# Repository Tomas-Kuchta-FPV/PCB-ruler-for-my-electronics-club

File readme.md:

# Thomases PCB ruler

So I run an electronics club in my chool and I want for the kids to have something fun. So I've figured that PCB rulers will cut ir, because we don't get many of these here.  
The front side has all of the basic schematic symbols, a ruller and a RFID detector.  
And what about the back side? It's pure ADHD riddeled with cool graphics, tables and more advanced footprints.  

## BOM
| Item               | Price ($)  | Link                                                      |
| ------------------ | ---------- | --------------------------------------------------------- |
| 0603 67R Rezistor  | Negligible | https://www.lcsc.com/product-detail/C2909394.html         |
| 0603 LED Diode     | Negligible | https://www.lcsc.com/product-detail/C19171394.html        |
| JLCPCB fabrication | 13.8       | https://cart.jlcpcb.com/quote                             |
| Duties and Taxes   | 8.2        | https://jlcpcb.com/shipping                               |
| Shipping           | 8.7        | https://jlcpcb.com/help/article/customs,-duties-and-taxes |
| Total              | 30.7       |

## Inspiration & Atribution
https://github.com/notaroomba/trace  
https://github.com/Small-doge128/swag-PCB-ruler  
Clipartt from https://www.svgrepo.com/collection/ionicons-filled-interface-icons/, https://www.svgrepo.com/collection/zest-interface-icons/ and https://www.svgrepo.com/collection/insects-1/

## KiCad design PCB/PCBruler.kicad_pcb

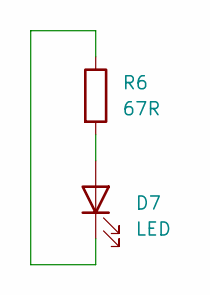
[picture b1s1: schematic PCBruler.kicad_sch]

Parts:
D7: LED; LED_0603_1608Metric
R6: 67R; R_0603_1608Metric_Pad0.98x0.95mm_HandSolder

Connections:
unnamed: D7.2 (A), R6.2
unnamed: D7.1 (K), R6.1

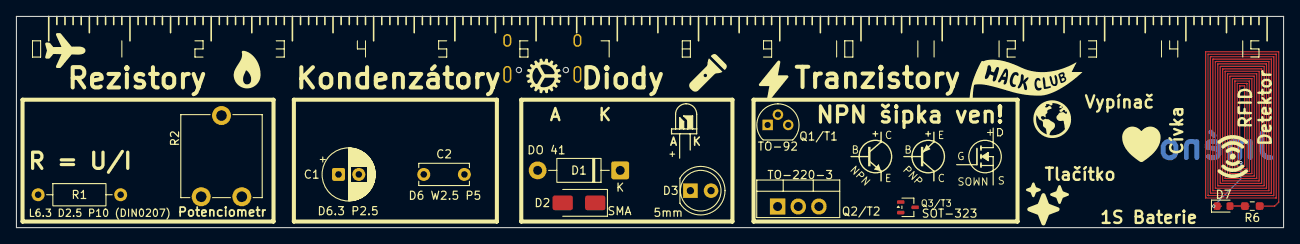
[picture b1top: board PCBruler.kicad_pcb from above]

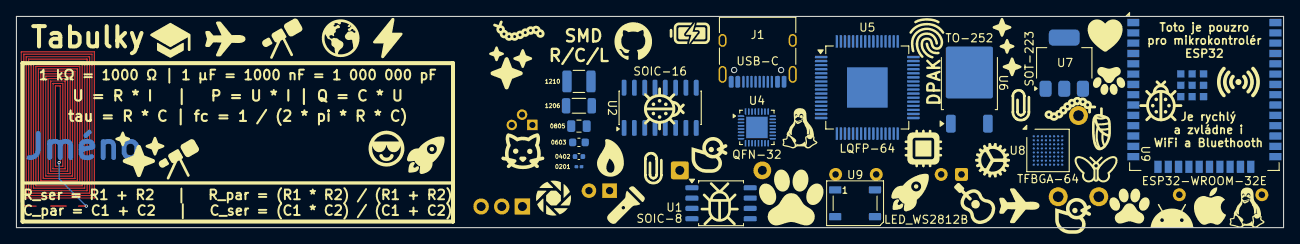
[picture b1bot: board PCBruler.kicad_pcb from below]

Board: 2 copper layers, 156.0 x 26.0 mm, 26 parts (10 on the bottom side), 2 nets.

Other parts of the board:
C1: CP_Radial_D6.3mm_P2.50mm
C2: C_Disc_D6.0mm_W2.5mm_P5.00mm
D1: D_DO-41_SOD81_P10.16mm_Horizontal
D2: D_SMA
D3: LED-GUIDE
D3#2: LED_D5.0mm
E$50: NMOS-SYMB
E$54: NPN-SYMB
E$59: PNP-SYMB
J1: USB_C_Receptacle_HRO_TYPE-C-31-M-12
Q1/T1: TO-92
Q2/T2: TO-220-3_Vertical
Q3/T3: SOT-323_SC-70
R1: R_Axial_DIN0207_L6.3mm_D2.5mm_P10.16mm_Horizontal
R2: Potentiometer_ACP_CA9-V10_Vertical
U1: SOIC-8_5.3x5.3mm_P1.27mm
U2: SOIC-16_3.9x9.9mm_P1.27mm
U4: QFN-32-1EP_4x4mm_P0.4mm_EP2.65x2.65mm
U5: LQFP-64-1EP_10x10mm_P0.5mm_EP5x5mm
U6: TO-252-2
U7: SOT-223
U8: TFBGA-64_5x5mm_Layout8x8_P0.5mm
U9: LED_WS2812B_PLCC4_5.0x5.0mm_P3.2mm
U9#2: ESP32-WROOM-32E
